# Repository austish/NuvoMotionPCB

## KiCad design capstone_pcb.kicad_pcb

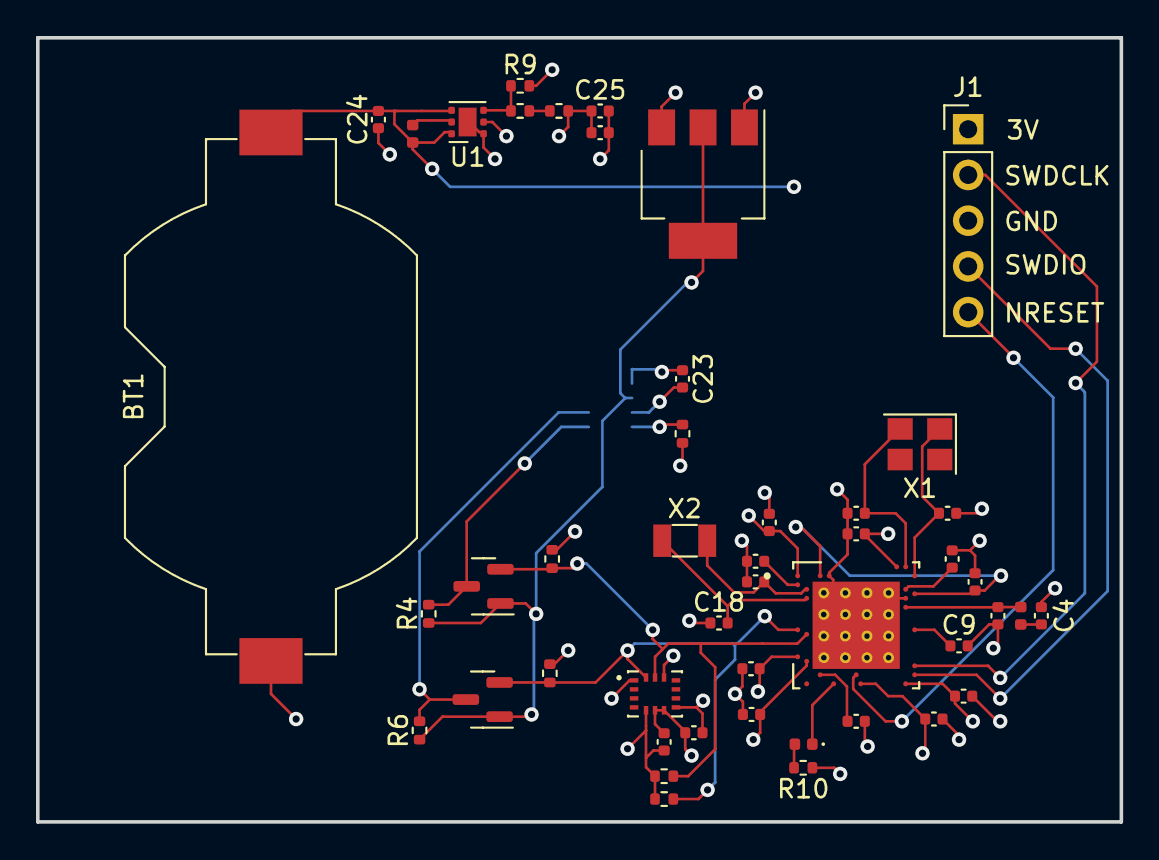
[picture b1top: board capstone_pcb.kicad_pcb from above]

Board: 4 copper layers, 60.2 x 43.6 mm, 48 parts (1 on the bottom side), 29 nets.

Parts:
BT1: Battery_Cell; BatteryHolder_Keystone_1058_1x2032
C1, C2, C17, C18: 12pF; C_0402_1005Metric
C3: 0.8pF; C_0402_1005Metric
C4: 0.5pF; C_0402_1005Metric
C5, C7, C8, C12, C16, C21, C23: 100nF; C_0402_1005Metric
C6, C19, C20: 4.7uF; C_0402_1005Metric
C9: 820pF; C_0402_1005Metric
C11: 100pF; C_0402_1005Metric
C14, C15: 1.0uF; C_0402_1005Metric
C24, C25, C26: 10uF; C_0402_1005Metric
D1: LED; LED_0402_1005Metric
IC6: BSS138; SOT-23
J1: Conn_01x05; PinHeader_1x05_P2.54mm_Vertical
L1: 4.7nH; L_0402_1005Metric
L2: 2.2uH; L_0402_1005Metric
Q1: BSS138; SOT-23
R1, R2: 4.7k; R_0402_1005Metric
R3, R4, R5, R6, R7: 10k; R_0402_1005Metric
R8, R9: 100k; R_0402_1005Metric
R10: 0.4k; R_0402_1005Metric
R11: 130k; R_0402_1005Metric
U1: TPS610994DRV; WSON-6-1EP_2x2mm_P0.65mm_EP1x1.6mm
U2: BMI270; XDCR_BMI270
U3: NRF52840-QIAA-R; XCVR_NRF52840-QIAA-R-edited
U4: MAX30102EFD+T; XDCR_MAX30101EFD_
U5: AMS1117-1.8; SOT-223-3_TabPin2
X1: 32MHz; Crystal_SMD_3225-4Pin_3.2x2.5mm
X2: 32.768kHz; Crystal_SMD_3215-2Pin_3.2x1.5mm

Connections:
+1V8: IC6.1 (G), Q1.1 (G), R4.1, R6.1, U4.11 (VDD), U5.2 (VO)
+3V: BT1.1 (+), C6.1, C7.1, C8.1, C12.1, C14.1, C19.1, C24.1, J1.1, L2.1, R10.1, U1.4 (EN), U1.6 (VI), U3.A22 (VDD), U3.AD14 (VDD), U3.AD23 (VDD), U3.B1 (VDD), U3.W1 (VDD), U3.Y2 (VDDH)
+3V3: C16.1, C21.1, C25.1, C26.1, R1.1, R2.1, R3.1, R5.1, R7.1, R11.1, U1.2 (VOUT), U2.5 (VDDIO), U2.8 (VDD), U2.12 (CSB), U5.3 (VI)
/BSCL: Q1.3 (D), R4.2, U4.2 (SCL)
/BSDA: IC6.3 (D), R6.2, U4.3 (SDA)
/DEC4 6: C15.1, U3.B5 (DEC4), U3.E24 (DEC2)
/RF: C4.1, L1.2
/SCL: Q1.2 (S), R1.2, R3.2, U2.13 (SCX), U3.P2 (P1.08)
/SDA: IC6.2 (S), R2.2, R5.2, U2.14 (SDX), U3.N1 (P0.08)
GND: BT1.2 (-), C1.1, C2.1, C3.2, C4.2, C5.2, C6.2, C7.2, C8.2, C9.2, C11.1, C12.2, C14.2, C15.2, C16.2, C17.1, C18.1, C19.2, C20.2, C21.2, C23.2, C24.2, C25.2, C26.2, J1.3, R9.2, U1.1 (GND), U1.7 (GND), U2.1 (SDO), U2.6 (GNDIO), U2.7 (GND), U3.74 (VSS), U3.B7 (VSS), U3.F23 (VSS_PA), U4.12 (GND), U5.1 (GND)
unnamed: C23.1, U4.9 (VLED+), U4.10 (VLED+)
unnamed: D1.2 (A), R10.2
unnamed: D1.1 (K), U3.AD8 (P0.13)
unnamed: J1.2, U3.AA24 (SWDCLK)
unnamed: J1.4, U3.AC24 (SWDIO)
unnamed: J1.5, U3.AC13 (P0.18/NRESET)
unnamed: R8.1, R11.2
unnamed: R8.2, R9.1, U1.3 (FB)
unnamed: L2.2, U1.5 (SW)
unnamed: C3.1, L1.1, U3.H23 (ANT)
unnamed: C5.1, U3.C1 (DEC1)
unnamed: C11.2, U3.D23 (DEC3)
unnamed: C9.1, U3.N24 (DEC5)
unnamed: C20.1, U3.AC5 (DECUSB)
unnamed: C17.2, U3.D2 (P0.00/XL1), X2.2
unnamed: C18.2, U3.F2 (P0.01/XL2), X2.1
unnamed: C1.2, U3.B24 (XC1), X1.1
unnamed: C2.2, U3.A23 (XC2), X1.2
unnamed: R7.2, U4.13 (*INT)

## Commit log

2026-03-14 New PCB
2026-03-14 update pcb layout
2026-03-15 add LCSC part numbers
2026-03-29 update pcb for final assembly
2026-04-05 new NRF
2026-04-05 exposed SWD pins and added LED for flashing status
2026-04-06 changed pin header
2026-04-06 add silkscreen labels to pin header
2026-04-08 added 100k and 130k resistors in series
2026-04-08 add 3.3v wire
2026-04-09 rearrange cap. and resist. to correct locations
2026-04-09 edit nrf pads and properties
2026-04-09 replaced nrf 3.3v w/ 3v, added 3v power plane
